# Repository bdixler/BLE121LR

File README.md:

# BLE121LR
Bluegiga BLE121LR breakout board

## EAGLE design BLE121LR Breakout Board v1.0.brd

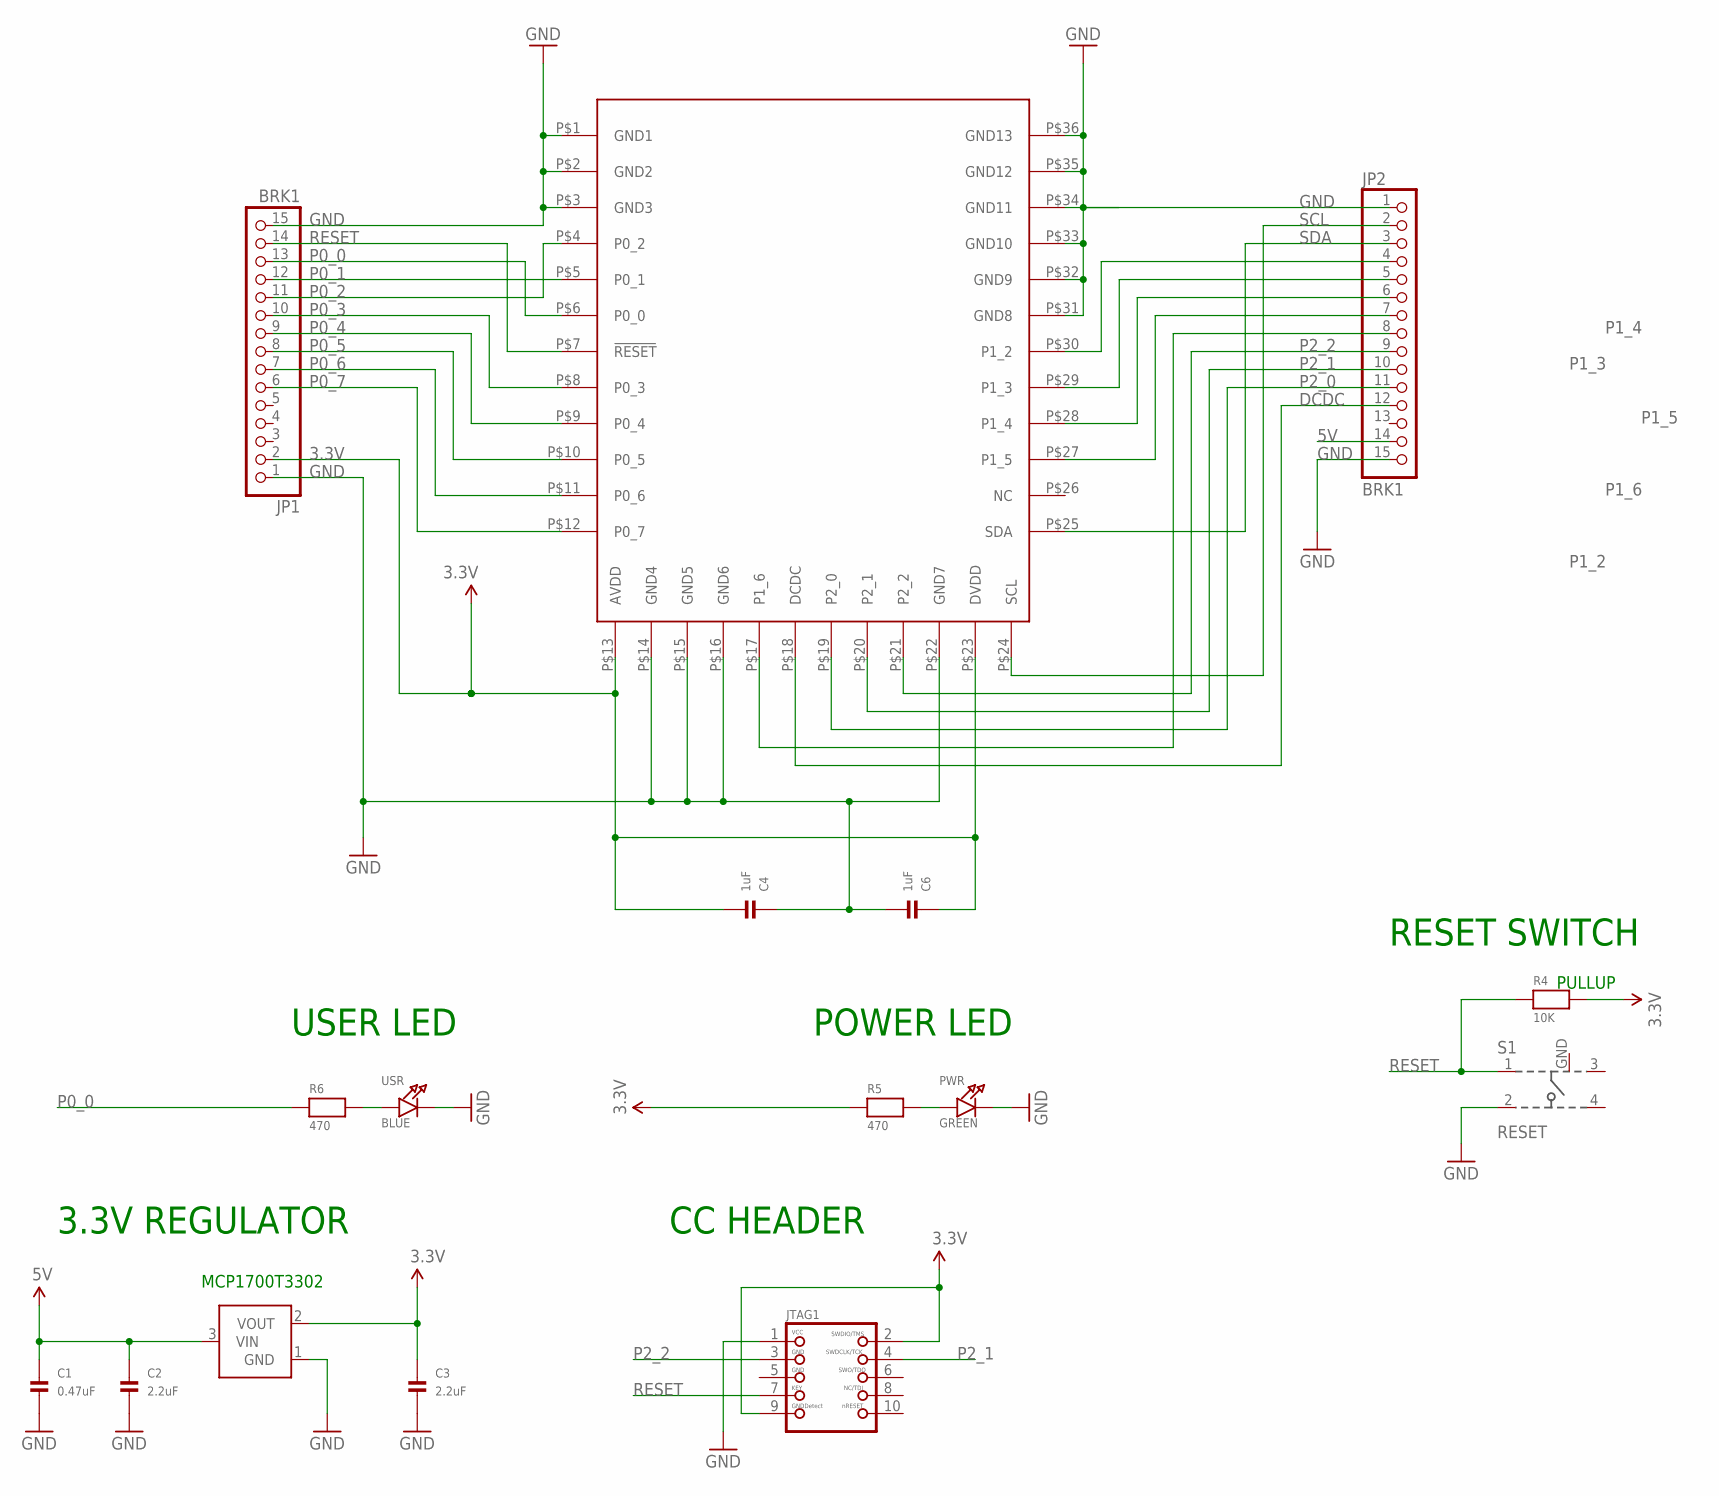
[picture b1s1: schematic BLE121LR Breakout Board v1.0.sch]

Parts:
C1: 0.47uF; 0603
C2, C3: 2.2uF; 0603
C4, C6: 1uF; 0603
JP1, JP2: BRK1; 1X15
JTAG1: JTAG-CORTEXM3; 2X05_1.27MM_SMT
PWR: GREEN; CHIPLED_0603
R4: 10K; 0603
R5, R6: 470; 0603
S1: RESET; 101-IG
U2: MCP1700; SOT23-3
U$3: BLE121LR
USR: BLUE; CHIPLED_0603

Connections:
3.3V: C3.1, C4.2, C6.1, JP1.2, JTAG1.2, JTAG1.9, R4.2, R5.1, U2.2 (VOUT), U$3.P$13 (AVDD), U$3.P$23 (DVDD)
5V: C1.1, C2.1, JP2.14, U2.3 (VIN)
DCDC: JP2.12, U$3.P$18 (DCDC)
GND: C1.2, C2.2, C3.2, C4.1, C6.2, JP1.1, JP1.15, JP2.1, JP2.15, JTAG1.1, PWR.C, S1.2, S1.GND, U2.1 (GND), U$3.P$1 (GND1), U$3.P$2 (GND2), U$3.P$3 (GND3), U$3.P$14 (GND4), U$3.P$15 (GND5), U$3.P$16 (GND6), U$3.P$22 (GND7), U$3.P$31 (GND8), U$3.P$32 (GND9), U$3.P$33 (GND10), U$3.P$34 (GND11), U$3.P$35 (GND12), U$3.P$36 (GND13), USR.C
unnamed: PWR.A, R5.2
unnamed: R6.2, USR.A
P0_0: JP1.13, R6.1, U$3.P$6 (P0_0)
P0_1: JP1.12, U$3.P$5 (P0_1)
P0_2: JP1.11, U$3.P$4 (P0_2)
P0_3: JP1.10, U$3.P$8 (P0_3)
P0_4: JP1.9, U$3.P$9 (P0_4)
P0_5: JP1.8, U$3.P$10 (P0_5)
P0_6: JP1.7, U$3.P$11 (P0_6)
P0_7: JP1.6, U$3.P$12 (P0_7)
P1_2: JP2.4, U$3.P$30 (P1_2)
P1_3: JP2.5, U$3.P$29 (P1_3)
P1_4: JP2.6, U$3.P$28 (P1_4)
P1_5: JP2.7, U$3.P$27 (P1_5)
P1_6: JP2.8, U$3.P$17 (P1_6)
P2_0: JP2.11, U$3.P$19 (P2_0)
P2_1: JP2.10, JTAG1.4, U$3.P$20 (P2_1)
P2_2: JP2.9, JTAG1.3, U$3.P$21 (P2_2)
RESET: JP1.14, JTAG1.7, R4.1, S1.1, U$3.P$7 (!RESET)
SCL: JP2.2, U$3.P$24 (SCL)
SDA: JP2.3, U$3.P$25 (SDA)

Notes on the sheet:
POWER LED
USER LED
CC HEADER
3.3V REGULATOR
RESET SWITCH
PULLUP
MCP1700T3302

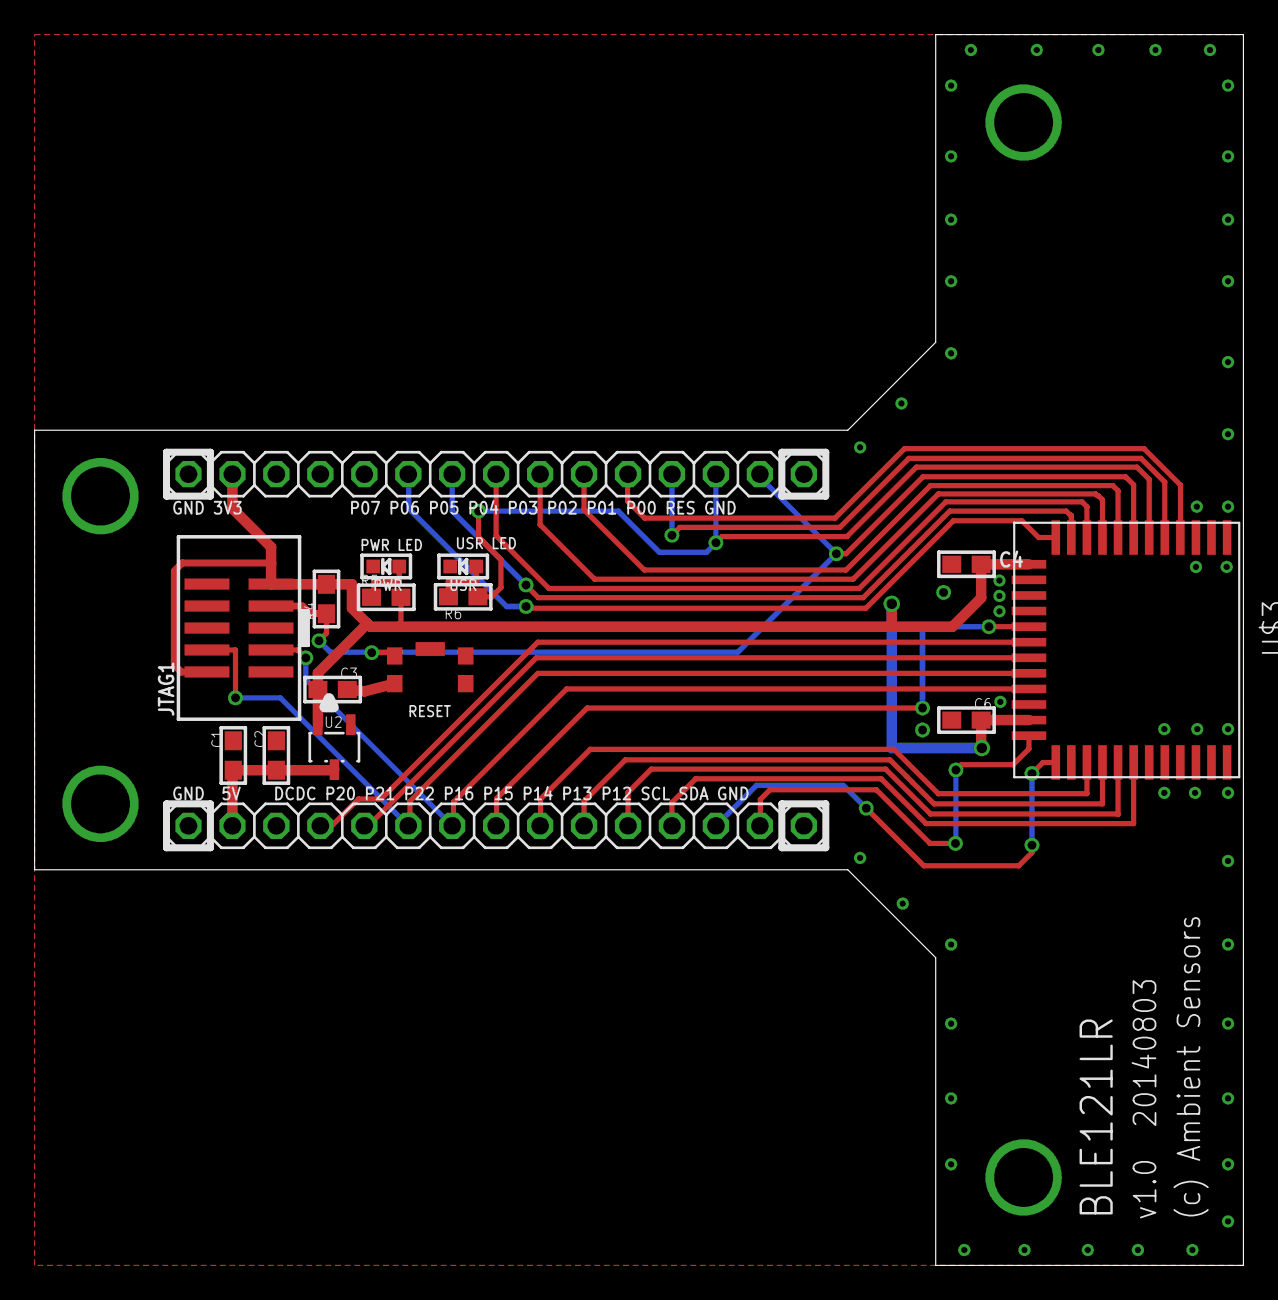
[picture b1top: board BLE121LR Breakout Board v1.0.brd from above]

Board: 2 copper layers, 69.8 x 71.1 mm, 16 parts (0 on the bottom side), 25 nets.

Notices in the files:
parts and their libraries:
microbuilder: This work is placed in the public domain, and may be freely used for commercial and non-commercial work with the following conditions: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
SparkFun: Licensing: CC v3.0 Share-Alike You are welcome to use this library for commercial purposes.
